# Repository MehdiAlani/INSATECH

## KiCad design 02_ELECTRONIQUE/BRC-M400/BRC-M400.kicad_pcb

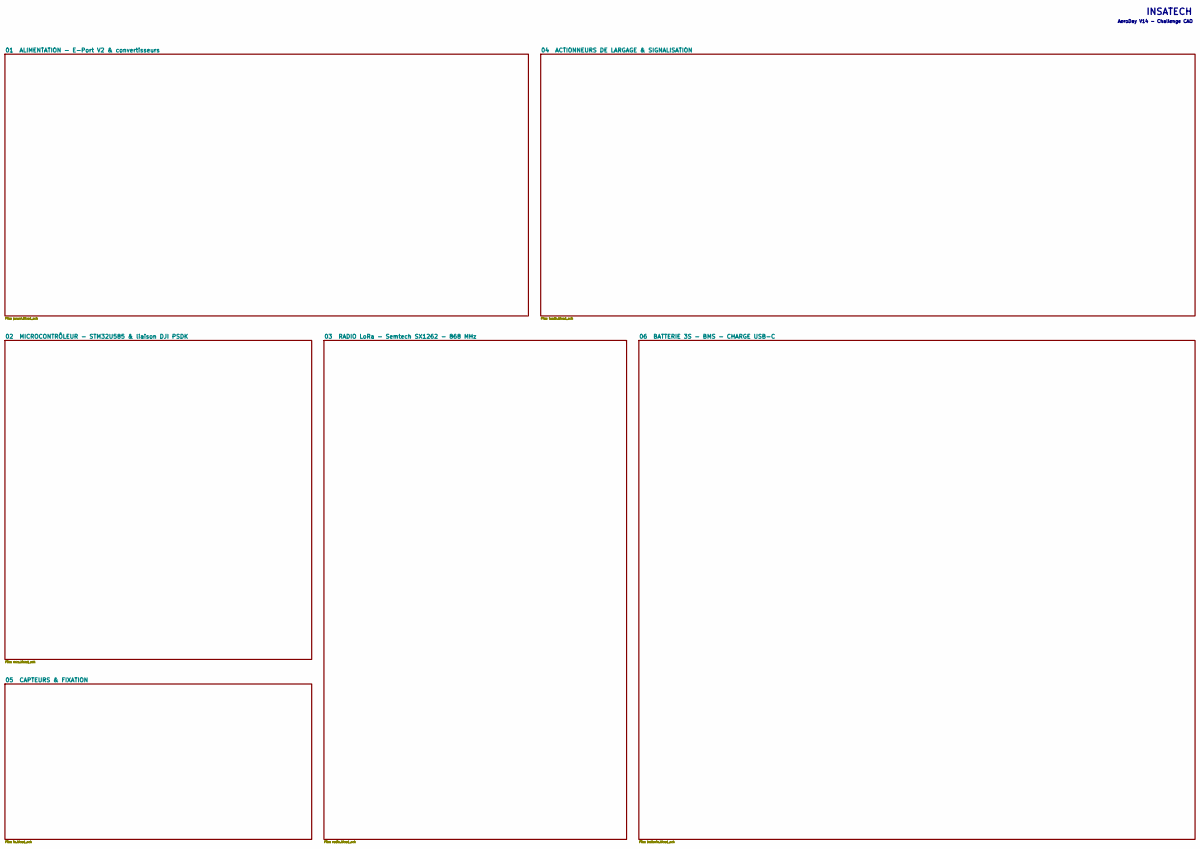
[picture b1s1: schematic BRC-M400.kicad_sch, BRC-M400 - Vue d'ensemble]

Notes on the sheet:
INSATECH
AeroDay V14 - Challenge CAO

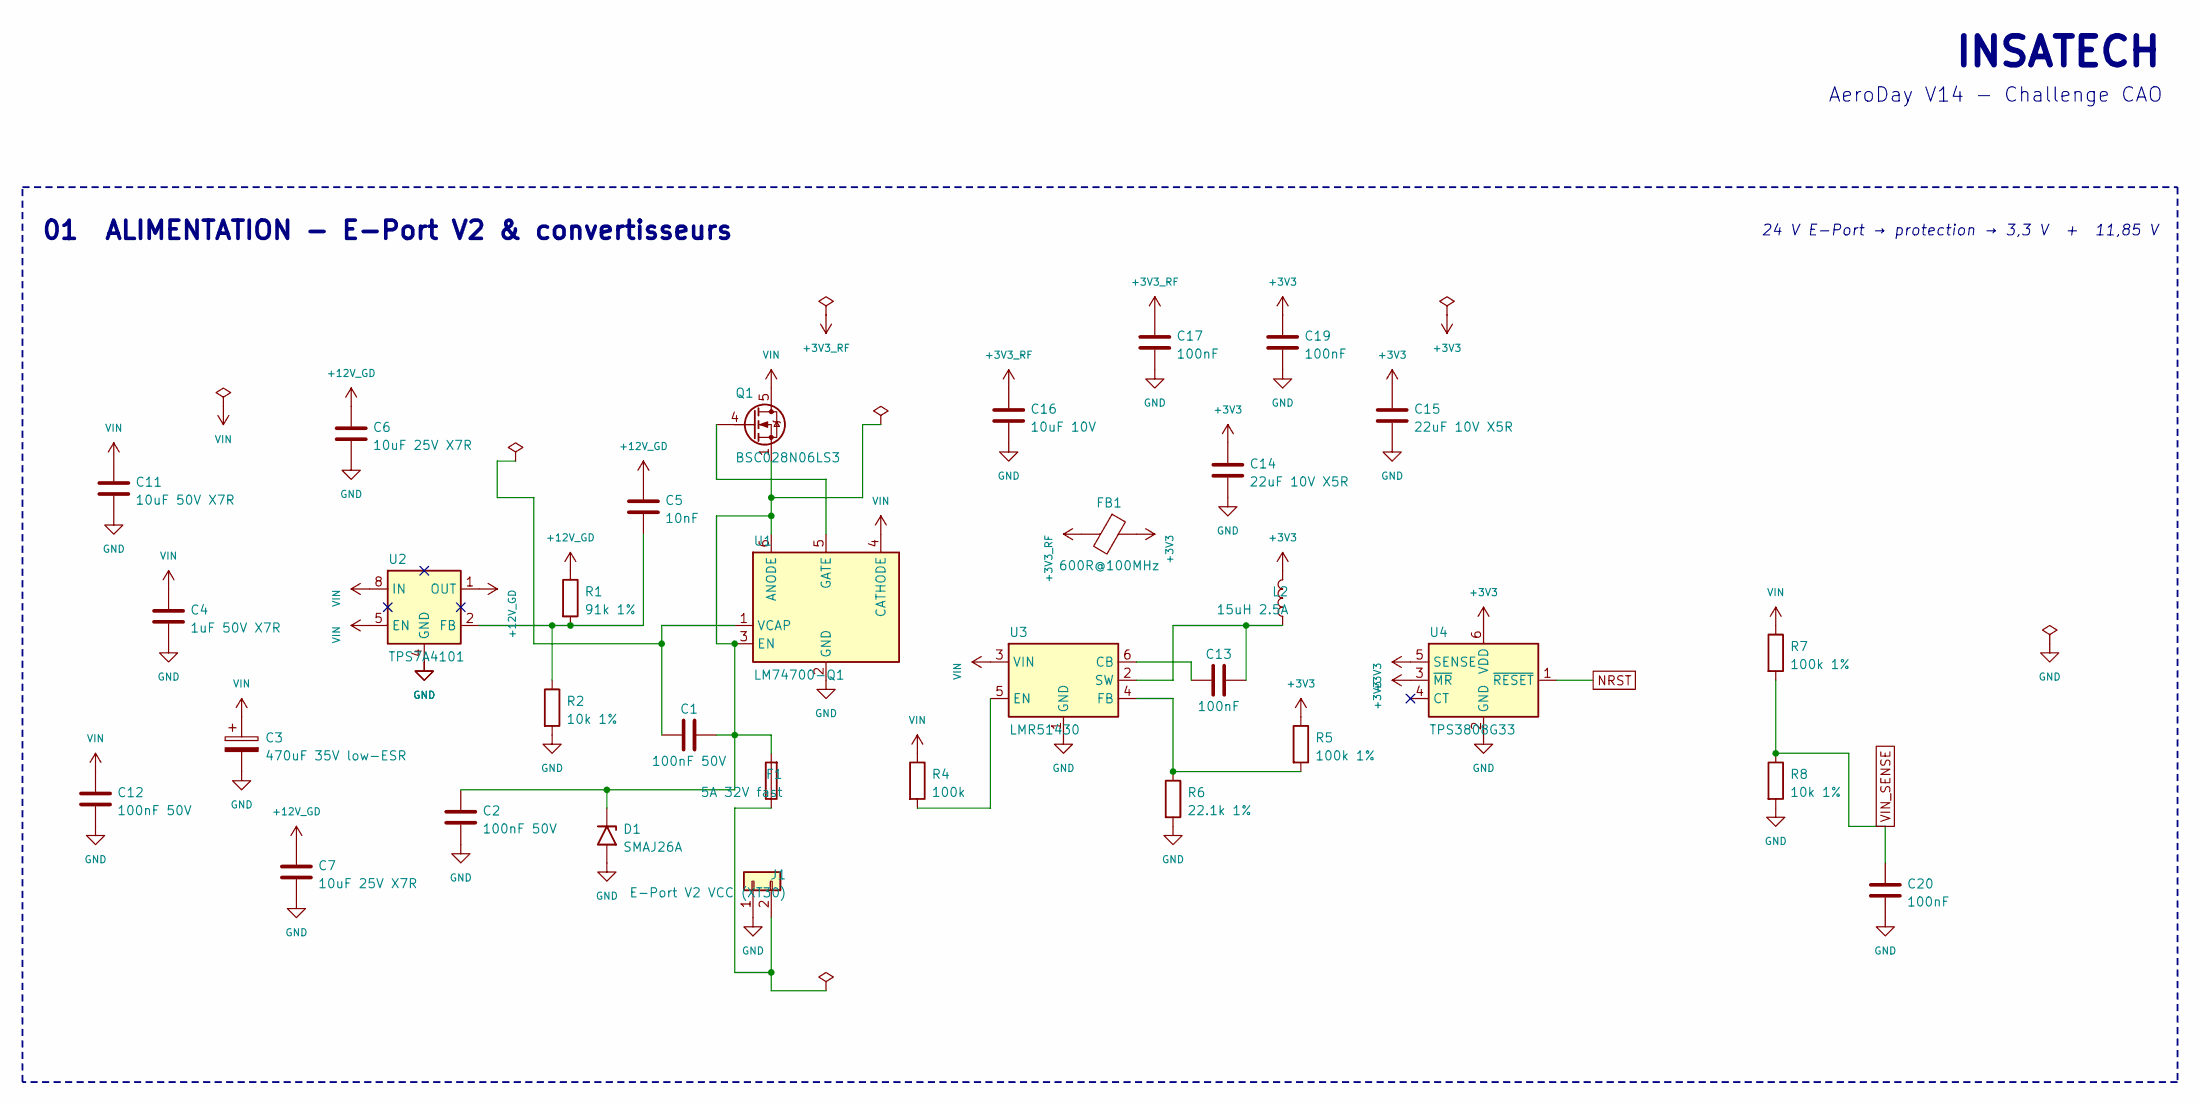
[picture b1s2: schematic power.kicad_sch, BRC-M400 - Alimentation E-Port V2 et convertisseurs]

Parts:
C1, C2, C12: 100nF 50V; C_0603_1608Metric
C3: 470uF 35V low-ESR; CP_Radial_D10.0mm_P5.00mm
C4: 1uF 50V X7R; C_0805_2012Metric
C5: 10nF; C_0603_1608Metric
C6, C7: 10uF 25V X7R; C_1210_3225Metric
C11: 10uF 50V X7R; C_1210_3225Metric
C13, C17, C19, C20: 100nF; C_0603_1608Metric
C14, C15: 22uF 10V X5R; C_1210_3225Metric
C16: 10uF 10V; C_0805_2012Metric
D1: SMAJ26A; D_SMA; MPN SMAJ26A
F1: 5A 32V fast; Fuse_1206_3216Metric; MPN 0466005.NR
FB1: 600R@100MHz; L_0603_1608Metric; MPN BLM18PG600SN1D
J1: E-Port V2 VCC (XT30); AMASS_XT30PW-M_1x02_P2.50mm_Horizontal; MPN XT30PW-M
L2: 15uH 2.5A; L_Bourns_SRN6045TA; MPN SRN6045TA-150M
Q1: BSC028N06LS3; TDSON-8-1; MPN BSC028N06LS3GATMA1
R1: 91k 1%; R_0603_1608Metric
R2, R8: 10k 1%; R_0603_1608Metric
R4: 100k; R_0603_1608Metric
R5, R7: 100k 1%; R_0603_1608Metric
R6: 22.1k 1%; R_0603_1608Metric
U1: LM74700-Q1; SOT-23-6; MPN LM74700QDBVRQ1
U2: TPS7A4101; Texas_DGN0008B_VSSOP-8-1EP_3x3mm_P0.65mm_EP2x3mm_Mask1.88x1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; MPN TPS7A4101DGNR
U3: LMR51430; SOT-23-6; MPN LMR51430XDDCR
U4: TPS3808G33; SOT-23-6; MPN TPS3808G33DBVR

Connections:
+3V3_RF: C16.1, C17.1, FB1.2; also elsewhere on the board
NRST: U4.1 (~RESET); also elsewhere on the board
unnamed: C1.2, C2.1, D1.1 (A1), F1.2, Q1.1 (S), Q1.2 (S), Q1.3 (S), U1.3 (EN), U1.6 (ANODE)
unnamed: Q1.4 (G), U1.5 (GATE)
unnamed: C1.1, U1.1 (VCAP)
unnamed: C13.1, U3.6 (CB)
unnamed: R4.2, U3.5 (EN)
unnamed: R5.2, R6.1, U3.4 (FB)
unnamed: C13.2, L2.1, U3.2 (SW)
PACK_P: F1.1, J1.2; also elsewhere on the board
VIN_SENSE: C20.1, R7.2, R8.1; also elsewhere on the board

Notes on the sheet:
INSATECH
AeroDay V14 - Challenge CAO
01 ALIMENTATION - E-Port V2 & convertisseurs
24 V E-Port → protection → 3,3 V + 11,85 V

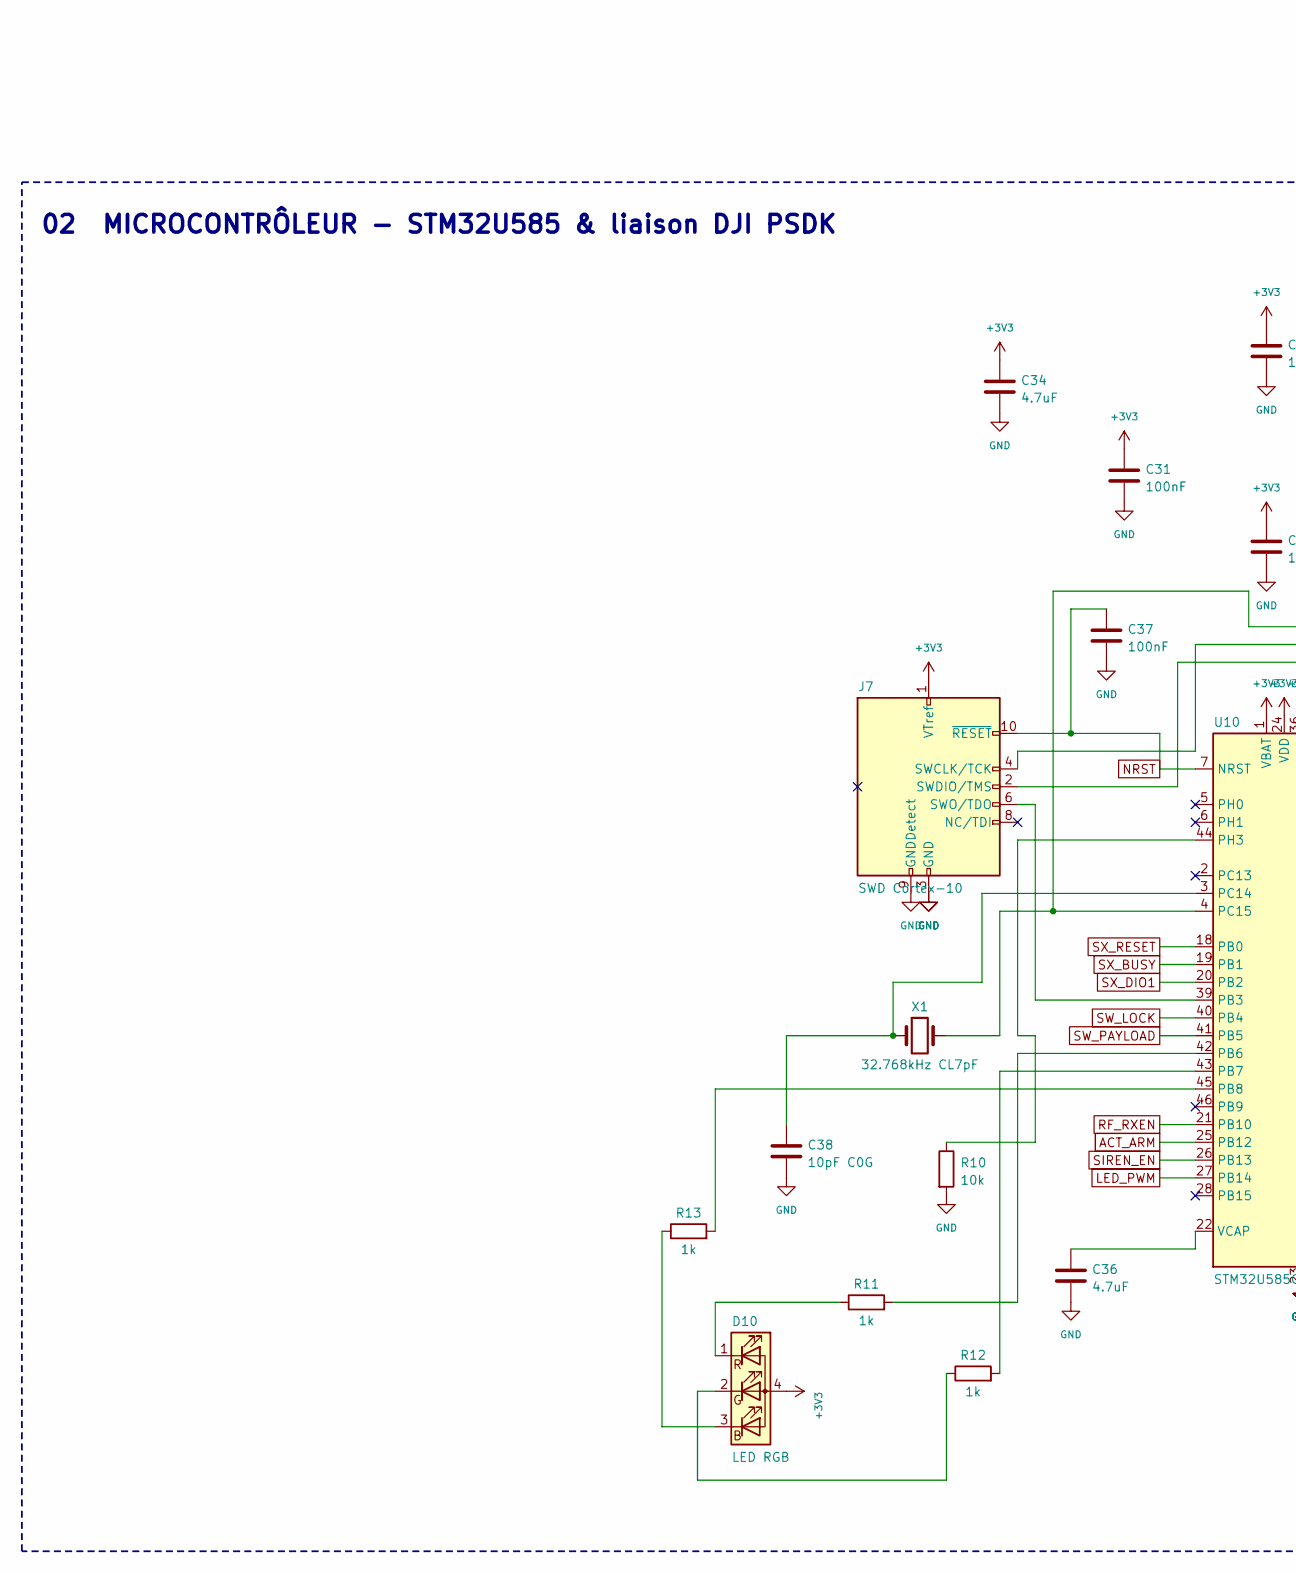
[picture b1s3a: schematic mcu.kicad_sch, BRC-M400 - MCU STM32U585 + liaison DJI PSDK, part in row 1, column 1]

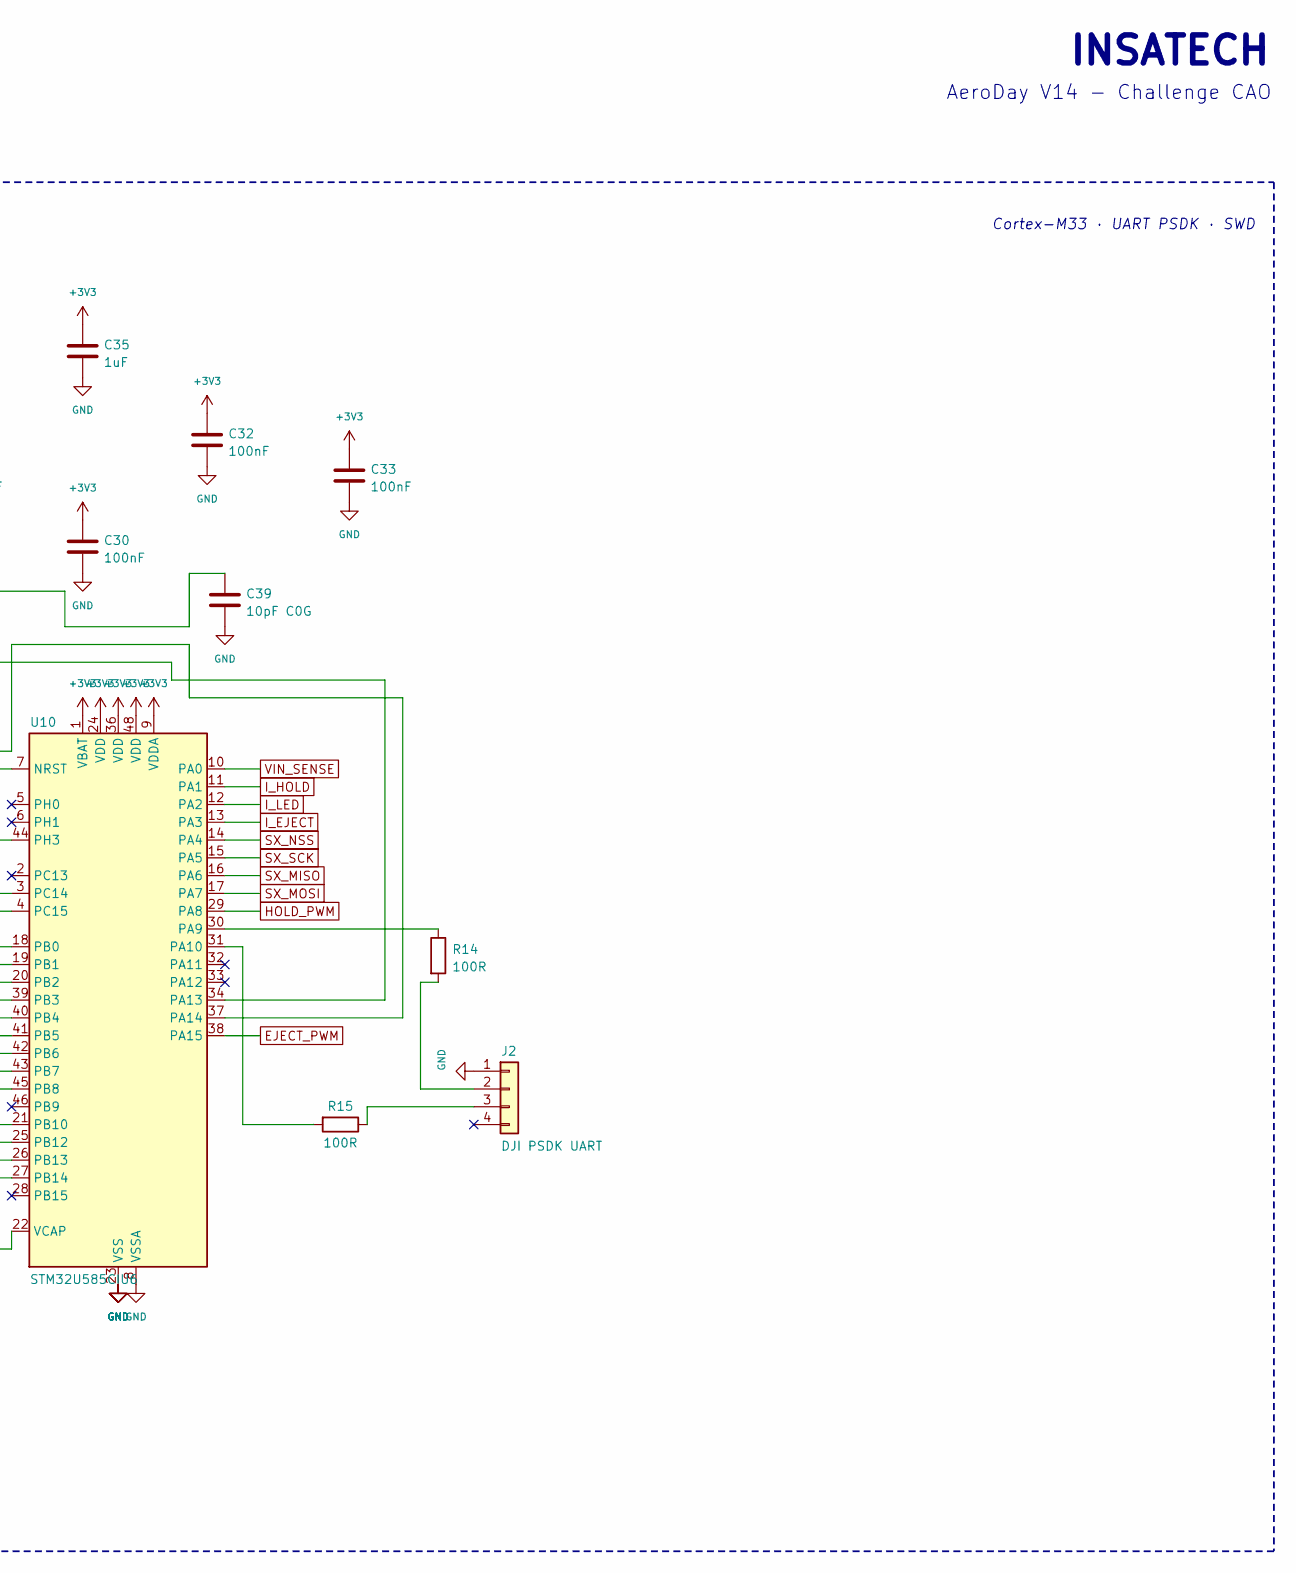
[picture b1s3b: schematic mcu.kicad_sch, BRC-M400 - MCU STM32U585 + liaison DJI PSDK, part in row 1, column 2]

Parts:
C30, C31, C32, C33, C37: 100nF; C_0402_1005Metric
C34, C36: 4.7uF; C_0603_1608Metric
C35: 1uF; C_0402_1005Metric
C38, C39: 10pF C0G; C_0402_1005Metric
D10: LED RGB; LED_RGB_1210
J2: DJI PSDK UART; JST_GH_SM04B-GHS-TB_1x04-1MP_P1.25mm_Horizontal; MPN SM04B-GHS-TB
J7: SWD Cortex-10; PinHeader_2x05_P1.27mm_Vertical
R10: 10k; R_0402_1005Metric
R11, R12, R13: 1k; R_0402_1005Metric
R14, R15: 100R; R_0402_1005Metric
U10: STM32U585CIU6; QFN-48-1EP_7x7mm_P0.5mm_EP5.6x5.6mm; MPN STM32U585CIU6
X1: 32.768kHz CL7pF; Crystal_SMD_3215-2Pin_3.2x1.5mm; MPN ABS07-120-32.768KHZ-T

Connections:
ACT_ARM: U10.25 (PB12); also elsewhere on the board
BMS_ALERT: U10.32 (PA11); also elsewhere on the board
CHG_STAT: U10.33 (PA12); also elsewhere on the board
EJECT_PWM: U10.38 (PA15); also elsewhere on the board
HOLD_PWM: U10.29 (PA8); also elsewhere on the board
I2C_SCL: R14.1, U10.30 (PA9); also elsewhere on the board
I2C_SDA: R15.2, U10.31 (PA10); also elsewhere on the board
I_EJECT: U10.13 (PA3); also elsewhere on the board
I_HOLD: U10.11 (PA1); also elsewhere on the board
I_LED: U10.12 (PA2); also elsewhere on the board
LED_PWM: U10.27 (PB14); also elsewhere on the board
NRST: C37.1, J7.10 (~RESET), U10.7 (NRST); also elsewhere on the board
unnamed: D10.3 (BK), R13.1
unnamed: D10.2 (GK), R12.1
unnamed: D10.1 (RK), R11.1
unnamed: J2.2, R14.2
unnamed: J2.3, R15.1
unnamed: J7.4 (SWCLK/TCK), U10.37 (PA14)
unnamed: J7.2 (SWDIO/TMS), U10.34 (PA13)
unnamed: J7.6 (SWO/TDO), U10.39 (PB3)
unnamed: R11.2, U10.42 (PB6)
unnamed: R12.2, U10.43 (PB7)
unnamed: R13.2, U10.45 (PB8)
unnamed: C38.1, U10.3 (PC14), X1.1
unnamed: C39.1, U10.4 (PC15), X1.2
unnamed: R10.1, U10.44 (PH3)
unnamed: C36.1, U10.22 (VCAP)
RF_RXEN: U10.21 (PB10); also elsewhere on the board
SIREN_EN: U10.26 (PB13); also elsewhere on the board
SW_LOCK: U10.40 (PB4); also elsewhere on the board
SW_PAYLOAD: U10.41 (PB5); also elsewhere on the board
SX_BUSY: U10.19 (PB1); also elsewhere on the board
SX_DIO1: U10.20 (PB2); also elsewhere on the board
SX_MISO: U10.16 (PA6); also elsewhere on the board
SX_MOSI: U10.17 (PA7); also elsewhere on the board
SX_NSS: U10.14 (PA4); also elsewhere on the board
SX_RESET: U10.18 (PB0); also elsewhere on the board
SX_SCK: U10.15 (PA5); also elsewhere on the board
VIN_SENSE: U10.10 (PA0); also elsewhere on the board

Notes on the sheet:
INSATECH
AeroDay V14 - Challenge CAO
02 MICROCONTRÔLEUR - STM32U585 & liaison DJI PSDK
Cortex-M33 · UART PSDK · SWD

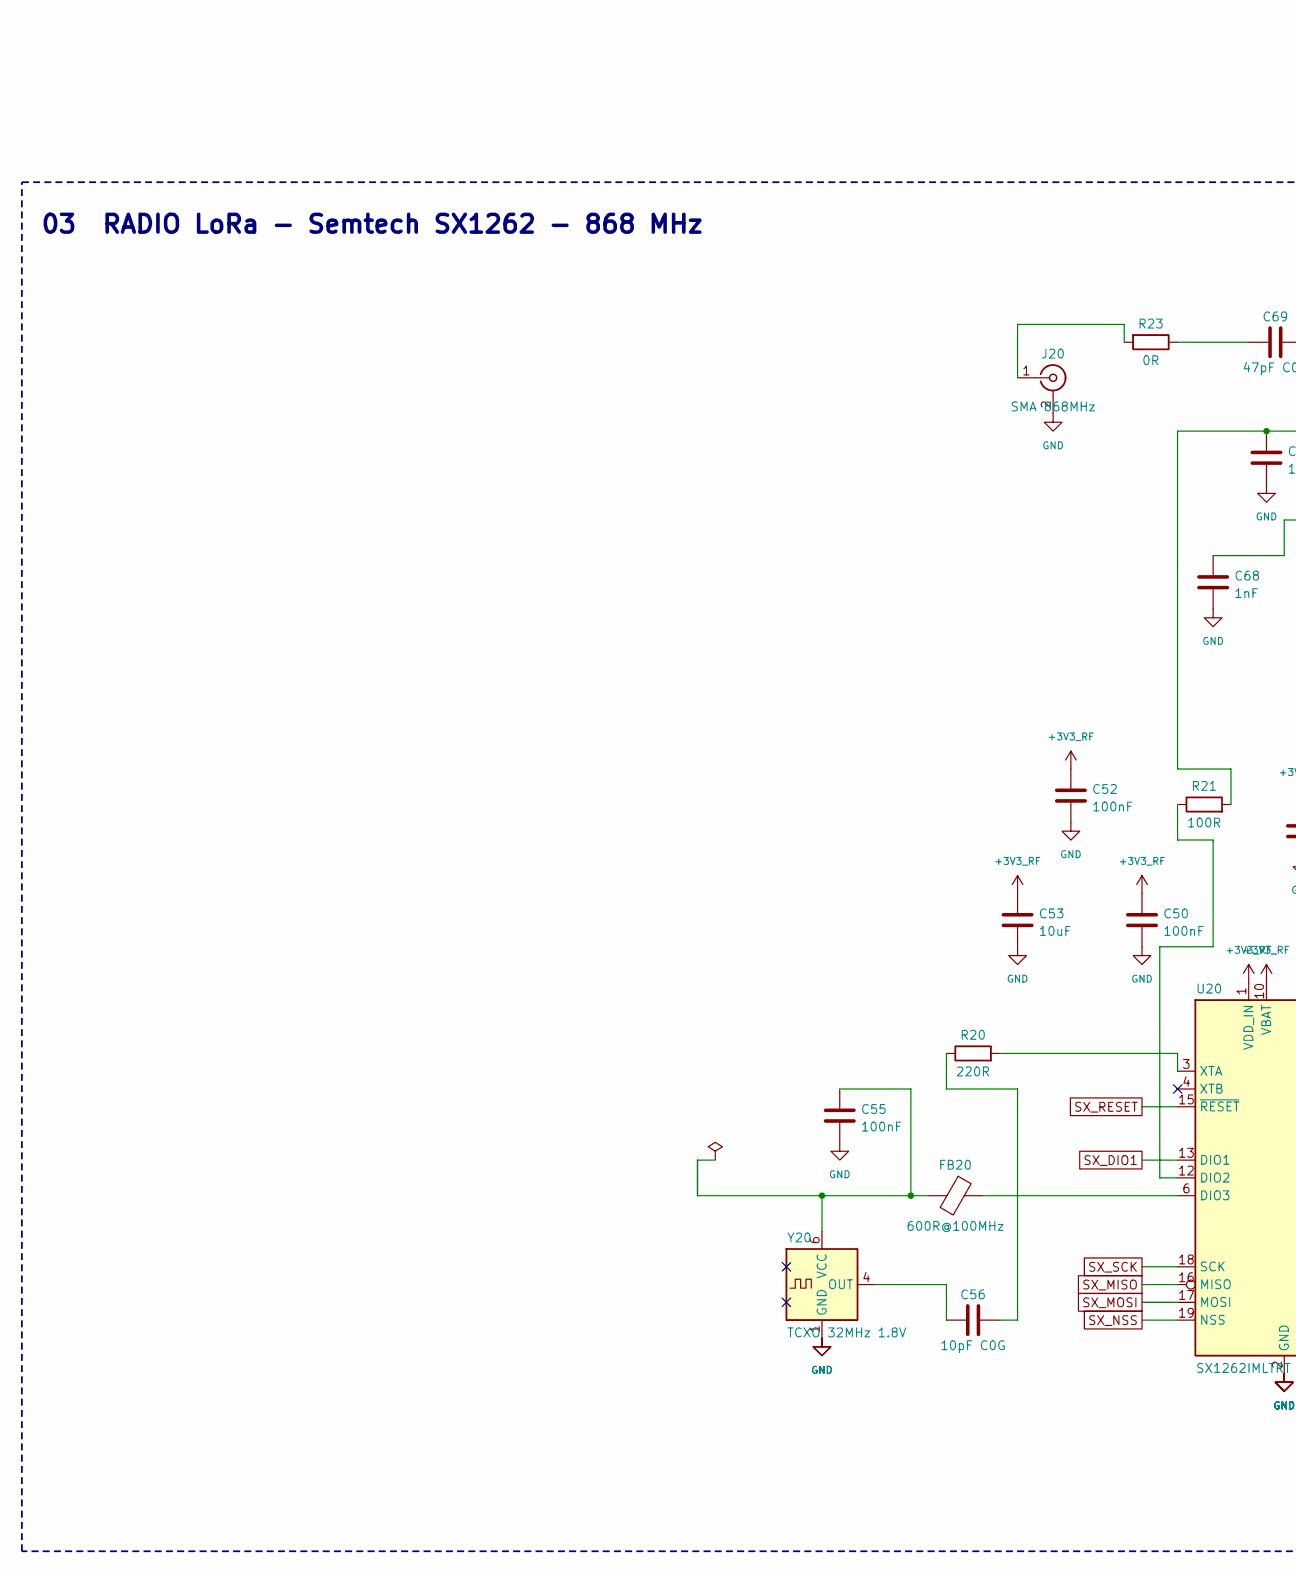
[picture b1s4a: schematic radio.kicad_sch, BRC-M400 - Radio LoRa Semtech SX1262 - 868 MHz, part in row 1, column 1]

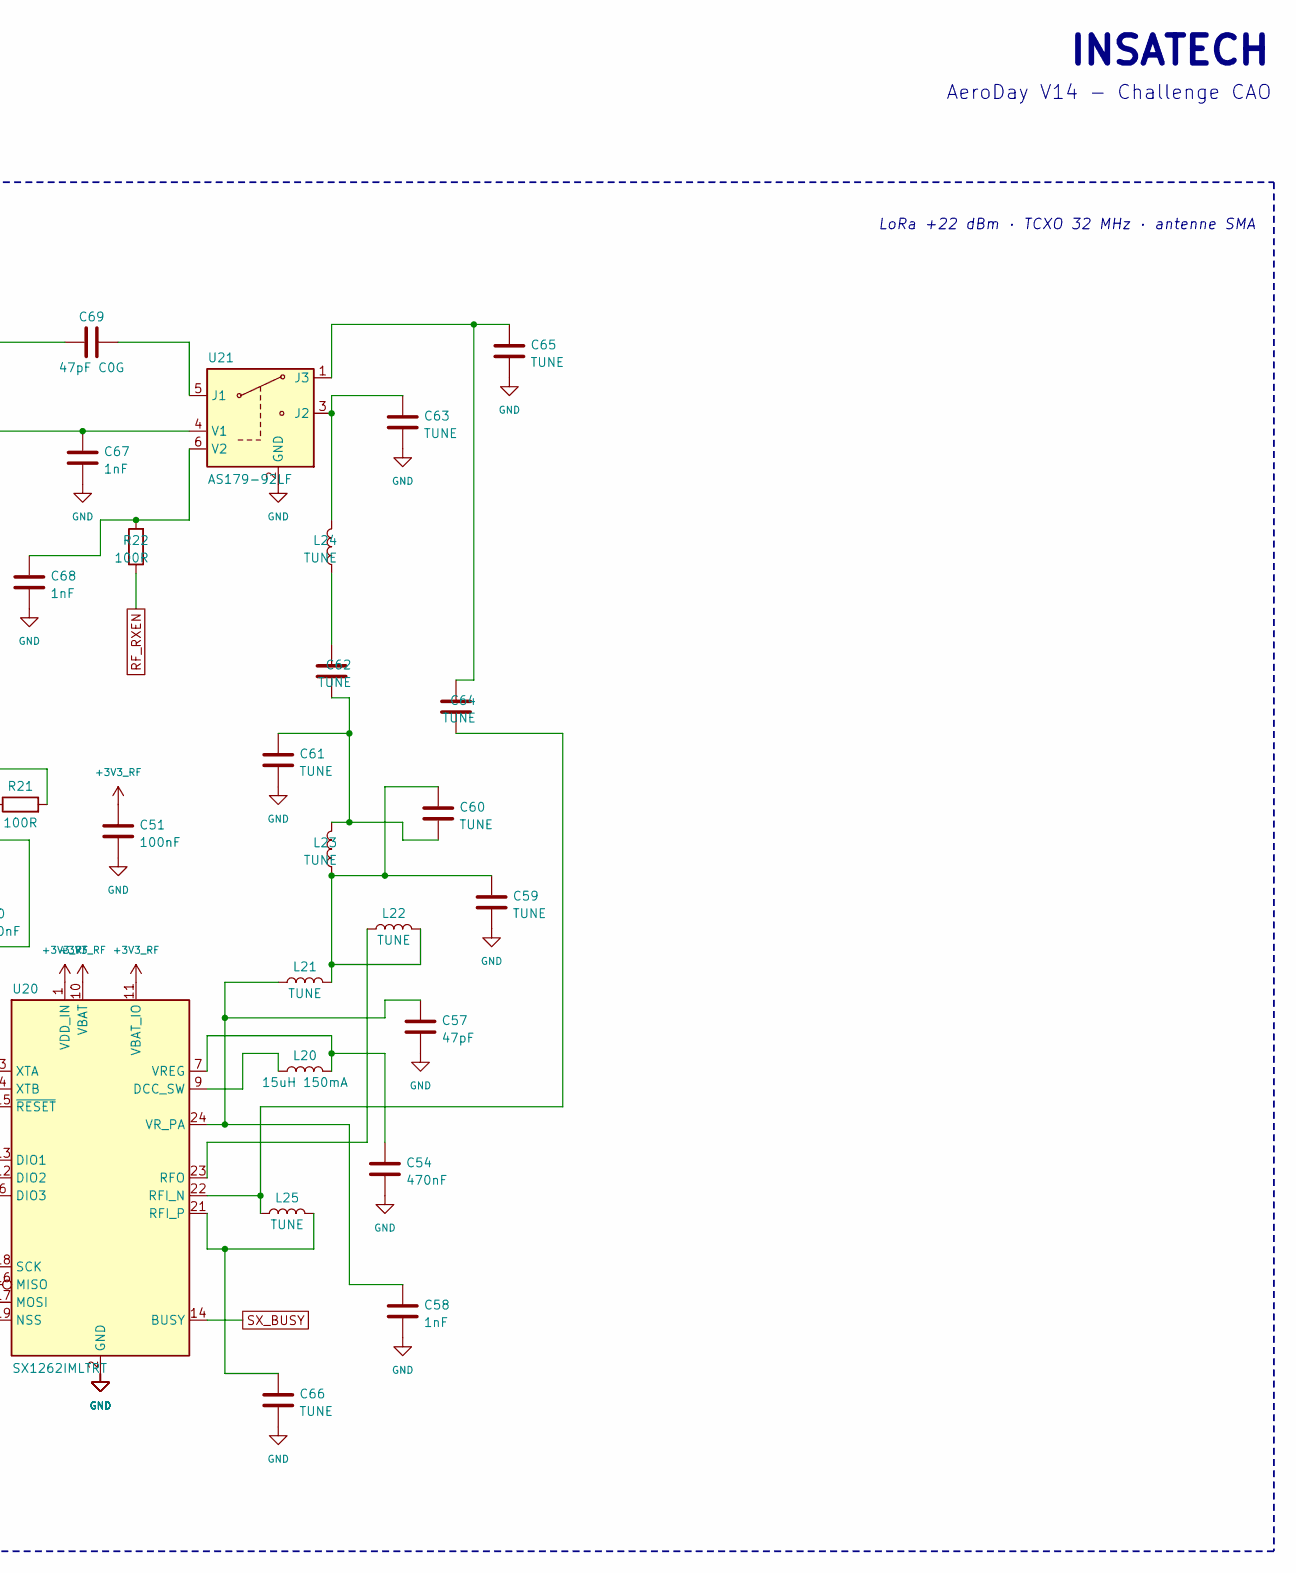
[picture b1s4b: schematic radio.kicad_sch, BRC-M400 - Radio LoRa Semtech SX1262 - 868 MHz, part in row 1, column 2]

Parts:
C50, C51, C52, C55: 100nF; C_0402_1005Metric
C53: 10uF; C_0805_2012Metric
C54: 470nF; C_0402_1005Metric
C56: 10pF C0G; C_0402_1005Metric
C57: 47pF; C_0402_1005Metric
C58, C67, C68: 1nF; C_0402_1005Metric
C59, C60, C61, C62, C63, C64, C65, C66: TUNE; C_0402_1005Metric
C69: 47pF C0G; C_0402_1005Metric
FB20: 600R@100MHz; L_0402_1005Metric
J20: SMA 868MHz; SMA_Amphenol_132289_EdgeMount; MPN 132289
L20: 15uH 150mA; L_0805_2012Metric
L21, L22, L23, L24, L25: TUNE; L_0402_1005Metric
R20: 220R; R_0402_1005Metric
R21, R22: 100R; R_0402_1005Metric
R23: 0R; R_0402_1005Metric
U20: SX1262IMLTRT; QFN-24-1EP_4x4mm_P0.5mm_EP2.6x2.6mm; MPN SX1262IMLTRT
U21: AS179-92LF; SOT-363_SC-70-6; MPN AS179-92LF
Y20: TCXO 32MHz 1.8V; Oscillator_SMD_Kyocera_2520-6Pin_2.5x2.0mm

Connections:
+3V3_RF: C50.1, C51.1, C52.1, C53.1, U20.1 (VDD_IN), U20.10 (VBAT), U20.11 (VBAT_IO); also elsewhere on the board
unnamed: C56.2, R20.1
unnamed: C59.1, C60.1, L21.2, L22.2, L23.1
unnamed: C60.2, C61.1, C62.1, L23.2
unnamed: C62.2, L24.1
unnamed: C69.2, R23.1
unnamed: J20.1 (In), R23.2
unnamed: L20.1, U20.9 (DCC_SW)
unnamed: R21.1, U20.12 (DIO2)
unnamed: FB20.1, U20.6 (DIO3)
unnamed: C64.1, L25.1, U20.22 (RFI_N)
unnamed: C66.1, L25.2, U20.21 (RFI_P)
unnamed: L22.1, U20.23 (RFO)
unnamed: C54.1, L20.2, U20.7 (VREG)
unnamed: C57.1, C58.1, L21.1, U20.24 (VR_PA)
unnamed: R20.2, U20.3 (XTA)
unnamed: C69.1, U21.5 (J1)
unnamed: C63.1, L24.2, U21.3 (J2)
unnamed: C64.2, C65.1, U21.1 (J3)
unnamed: C67.1, R21.2, U21.4 (V1)
unnamed: C68.1, R22.2, U21.6 (V2)
unnamed: C56.1, Y20.4 (OUT)
unnamed: C55.1, FB20.2, Y20.6 (VCC)
RF_RXEN: R22.1; also elsewhere on the board
SX_BUSY: U20.14 (BUSY); also elsewhere on the board
SX_DIO1: U20.13 (DIO1); also elsewhere on the board
SX_MISO: U20.16 (MISO); also elsewhere on the board
SX_MOSI: U20.17 (MOSI); also elsewhere on the board
SX_NSS: U20.19 (NSS); also elsewhere on the board
SX_RESET: U20.15 (~RESET); also elsewhere on the board
SX_SCK: U20.18 (SCK); also elsewhere on the board

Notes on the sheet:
INSATECH
AeroDay V14 - Challenge CAO
03 RADIO LoRa - Semtech SX1262 - 868 MHz
LoRa +22 dBm · TCXO 32 MHz · antenne SMA

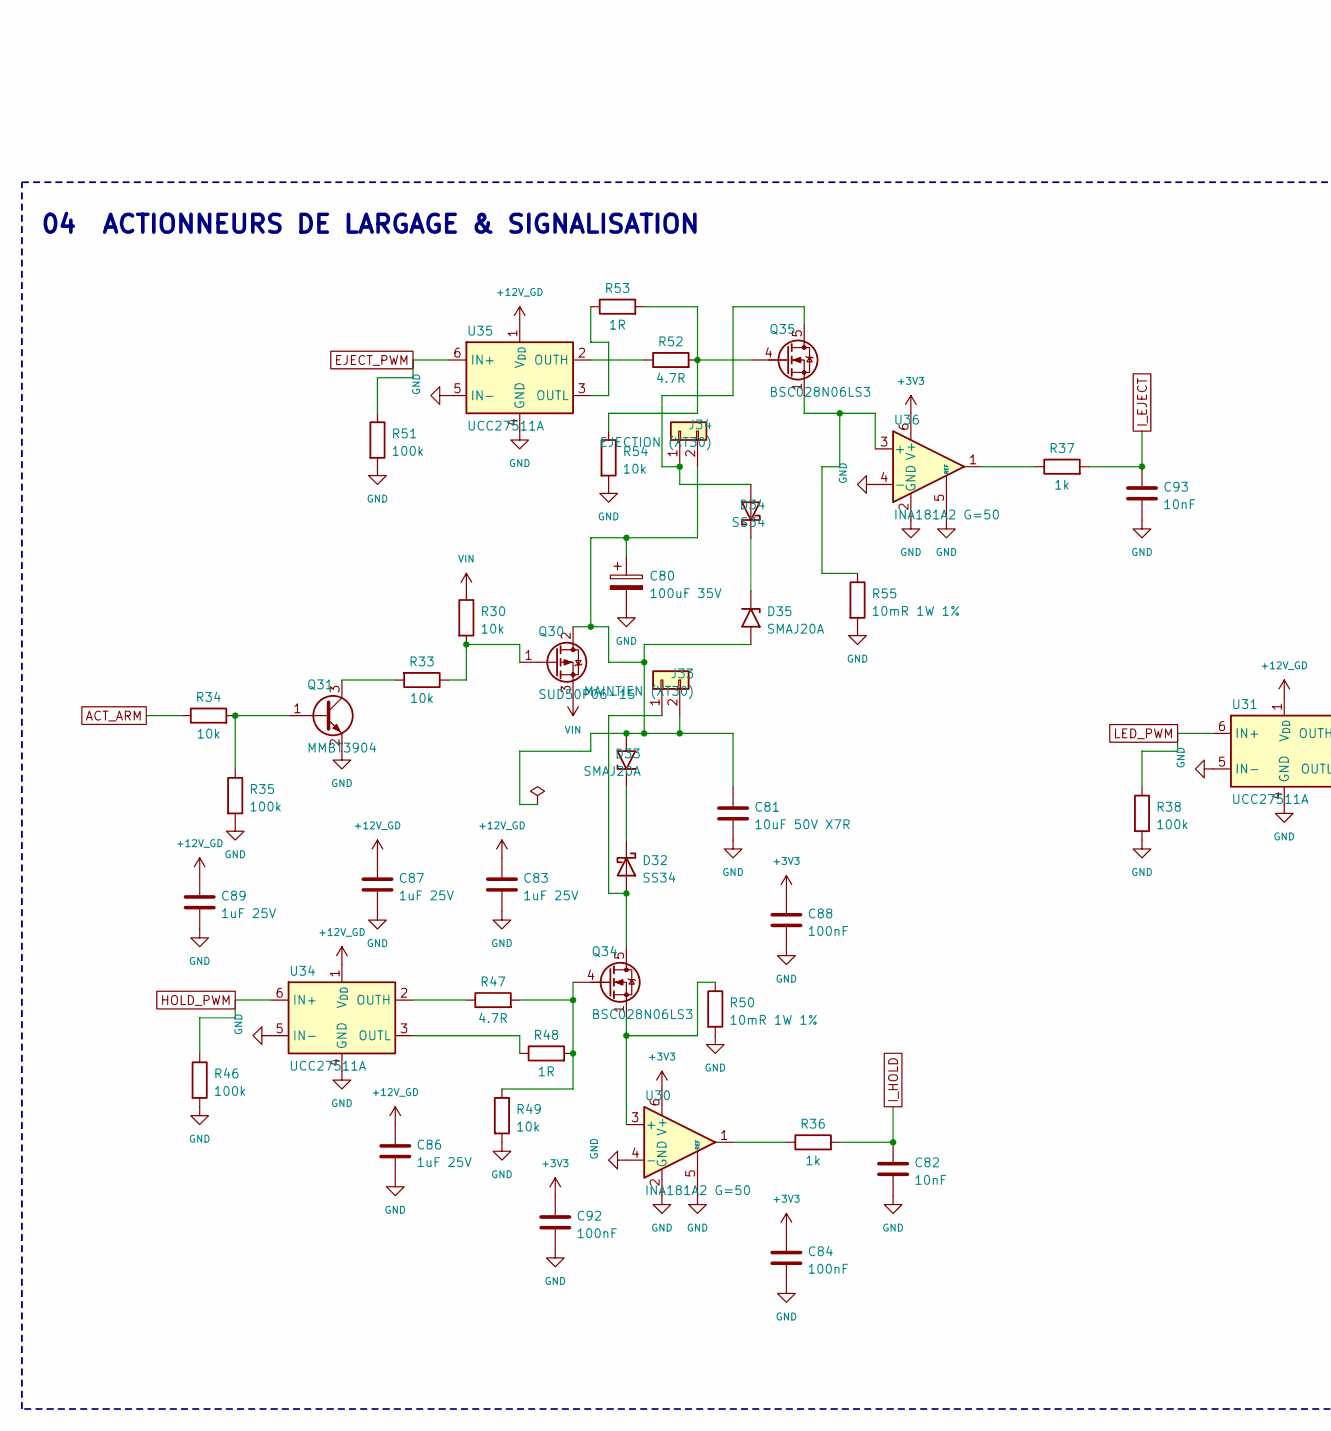
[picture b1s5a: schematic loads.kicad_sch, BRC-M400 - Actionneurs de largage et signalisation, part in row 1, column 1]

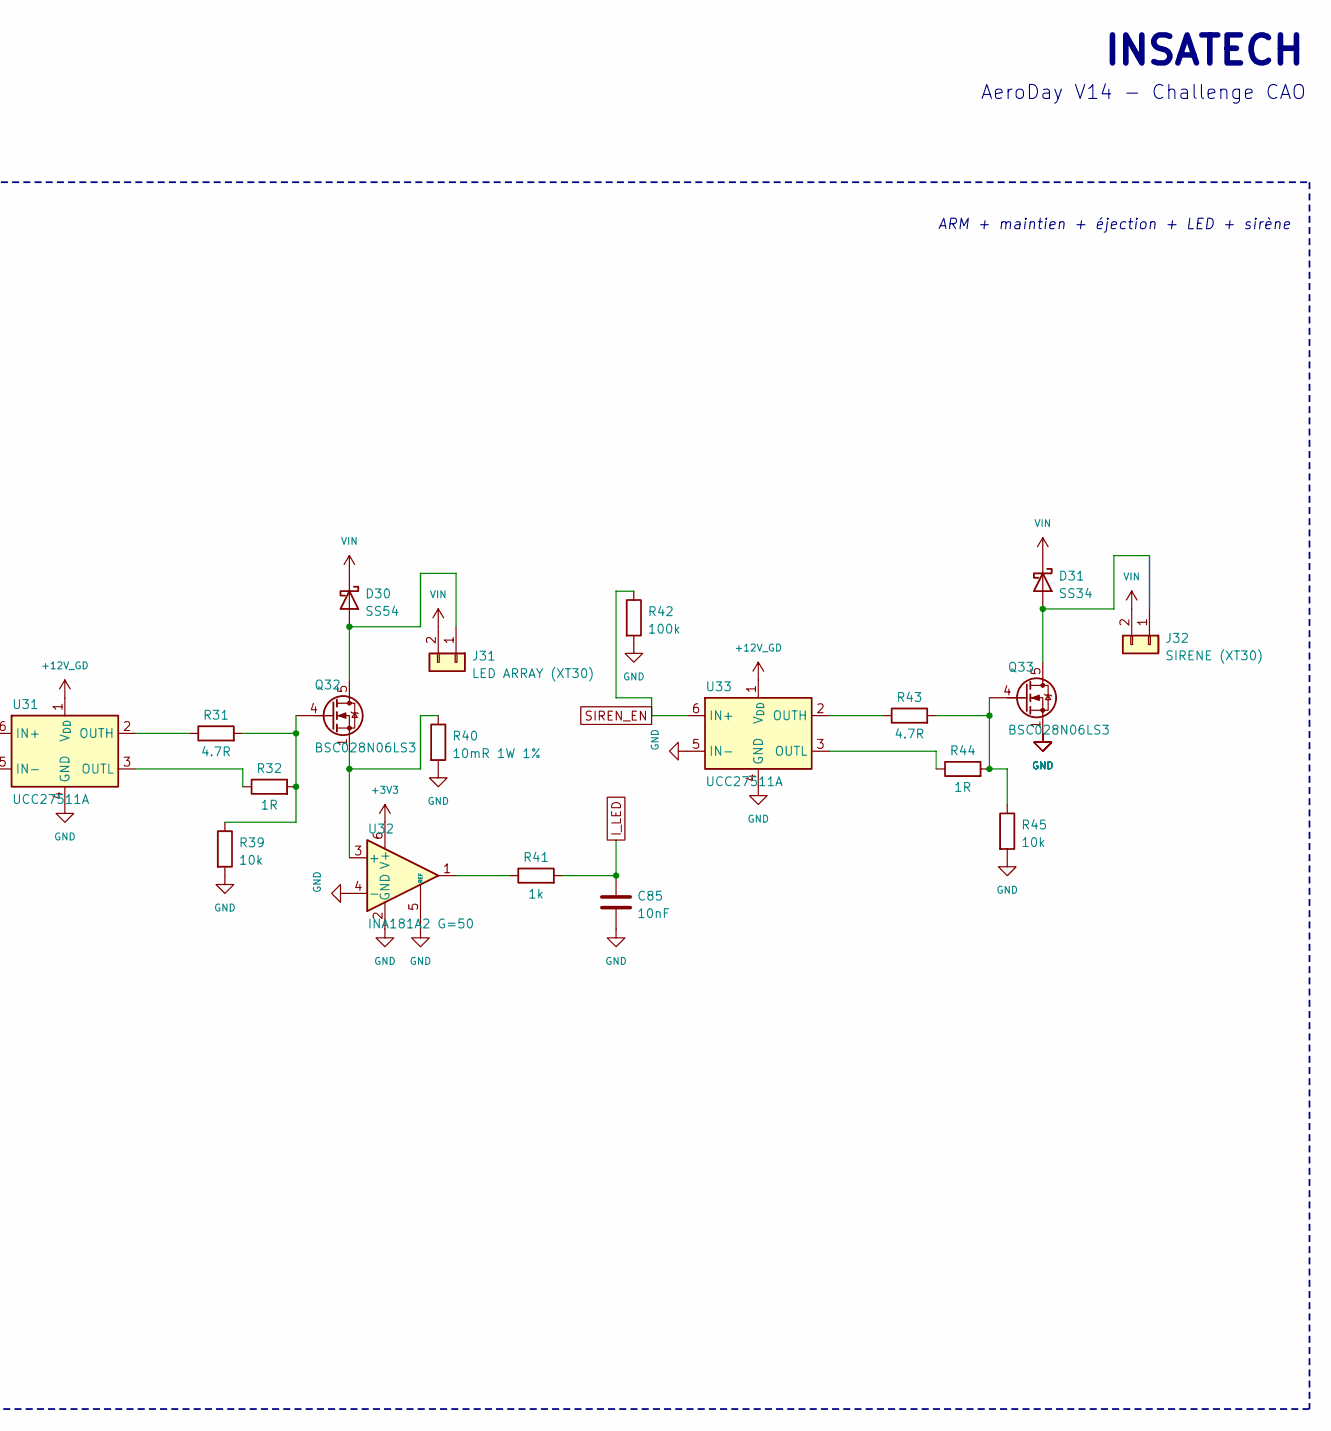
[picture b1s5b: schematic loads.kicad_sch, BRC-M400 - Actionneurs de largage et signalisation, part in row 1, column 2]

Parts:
C80: 100uF 35V; CP_Elec_8x10
C81: 10uF 50V X7R; C_1210_3225Metric
C82, C85, C93: 10nF; C_0603_1608Metric
C83, C86, C87, C89: 1uF 25V; C_0603_1608Metric
C84, C88, C92: 100nF; C_0603_1608Metric
D30: SS54; D_SMC; MPN SS54
D31, D32, D34: SS34; D_SMA; MPN SS34
D33, D35: SMAJ20A; D_SMA; MPN SMAJ20A
J31: LED ARRAY (XT30); AMASS_XT30PW-F_1x02_P2.50mm_Horizontal; MPN XT30PW-F
J32: SIRENE (XT30); AMASS_XT30PW-F_1x02_P2.50mm_Horizontal; MPN XT30PW-F
J33: MAINTIEN (XT30); AMASS_XT30PW-F_1x02_P2.50mm_Horizontal; MPN XT30PW-F
J34: EJECTION (XT30); AMASS_XT30PW-F_1x02_P2.50mm_Horizontal; MPN XT30PW-F
Q30: SUD50P06-15; TO-252-2; MPN SUD50P06-15-GE3
Q31: MMBT3904; SOT-23
Q32, Q33, Q34, Q35: BSC028N06LS3; TDSON-8-1; MPN BSC028N06LS3GATMA1
R30, R33, R34, R39, R45, R49, R54: 10k; R_0603_1608Metric
R31, R43, R47, R52: 4.7R; R_0603_1608Metric
R32, R44, R48, R53: 1R; R_0603_1608Metric
R35, R38, R42, R46, R51: 100k; R_0603_1608Metric
R36, R37, R41: 1k; R_0603_1608Metric
R40, R50, R55: 10mR 1W 1%; R_2512_6332Metric
U30, U32, U36: INA181A2 G=50; SOT-23-6; MPN INA181A2IDBVR
U31, U33, U34, U35: UCC27511A; SOT-23-6; MPN UCC27511ADBVR

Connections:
ACT_ARM: R34.1; also elsewhere on the board
EJECT_PWM: R51.1, U35.6 (IN+); also elsewhere on the board
HOLD_PWM: R46.1, U34.6 (IN+); also elsewhere on the board
I_EJECT: C93.1, R37.2; also elsewhere on the board
I_HOLD: C82.1, R36.2; also elsewhere on the board
I_LED: C85.1, R41.2; also elsewhere on the board
LED_PWM: R38.1, U31.6 (IN+); also elsewhere on the board
unnamed: D30.2 (A), J31.1, Q32.5 (D)
unnamed: D31.2 (A), J32.1, Q33.5 (D)
unnamed: D32.2 (A), J33.1, Q34.5 (D)
unnamed: D32.1 (K), D33.1 (A1)
unnamed: C80.1, C81.1, D33.2 (A2), D35.2 (A2), J33.2, J34.2, Q30.2 (D)
unnamed: D34.2 (A), J34.1, Q35.5 (D)
unnamed: D34.1 (K), D35.1 (A1)
unnamed: Q30.1 (G), R30.2, R33.1
unnamed: Q31.1 (B), R34.2, R35.1
unnamed: Q31.3 (C), R33.2
unnamed: Q32.4 (G), R31.2, R32.2, R39.1
unnamed: Q33.4 (G), R43.2, R44.2, R45.1
unnamed: Q34.4 (G), R47.2, R48.2, R49.1
unnamed: Q35.4 (G), R52.2, R53.2, R54.1
unnamed: R36.1, U30.1
unnamed: R37.1, U36.1
unnamed: R41.1, U32.1
unnamed: Q34.1 (S), Q34.2 (S), Q34.3 (S), R50.1, U30.3 (+)
unnamed: R31.1, U31.2 (OUTH)
unnamed: R32.1, U31.3 (OUTL)
unnamed: Q32.1 (S), Q32.2 (S), Q32.3 (S), R40.1, U32.3 (+)
unnamed: R43.1, U33.2 (OUTH)
unnamed: R44.1, U33.3 (OUTL)
unnamed: R47.1, U34.2 (OUTH)
unnamed: R48.1, U34.3 (OUTL)
unnamed: R52.1, U35.2 (OUTH)
unnamed: R53.1, U35.3 (OUTL)
unnamed: Q35.1 (S), Q35.2 (S), Q35.3 (S), R55.1, U36.3 (+)
SIREN_EN: R42.1, U33.6 (IN+); also elsewhere on the board

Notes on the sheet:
INSATECH
AeroDay V14 - Challenge CAO
04 ACTIONNEURS DE LARGAGE & SIGNALISATION
ARM + maintien + éjection + LED + sirène
